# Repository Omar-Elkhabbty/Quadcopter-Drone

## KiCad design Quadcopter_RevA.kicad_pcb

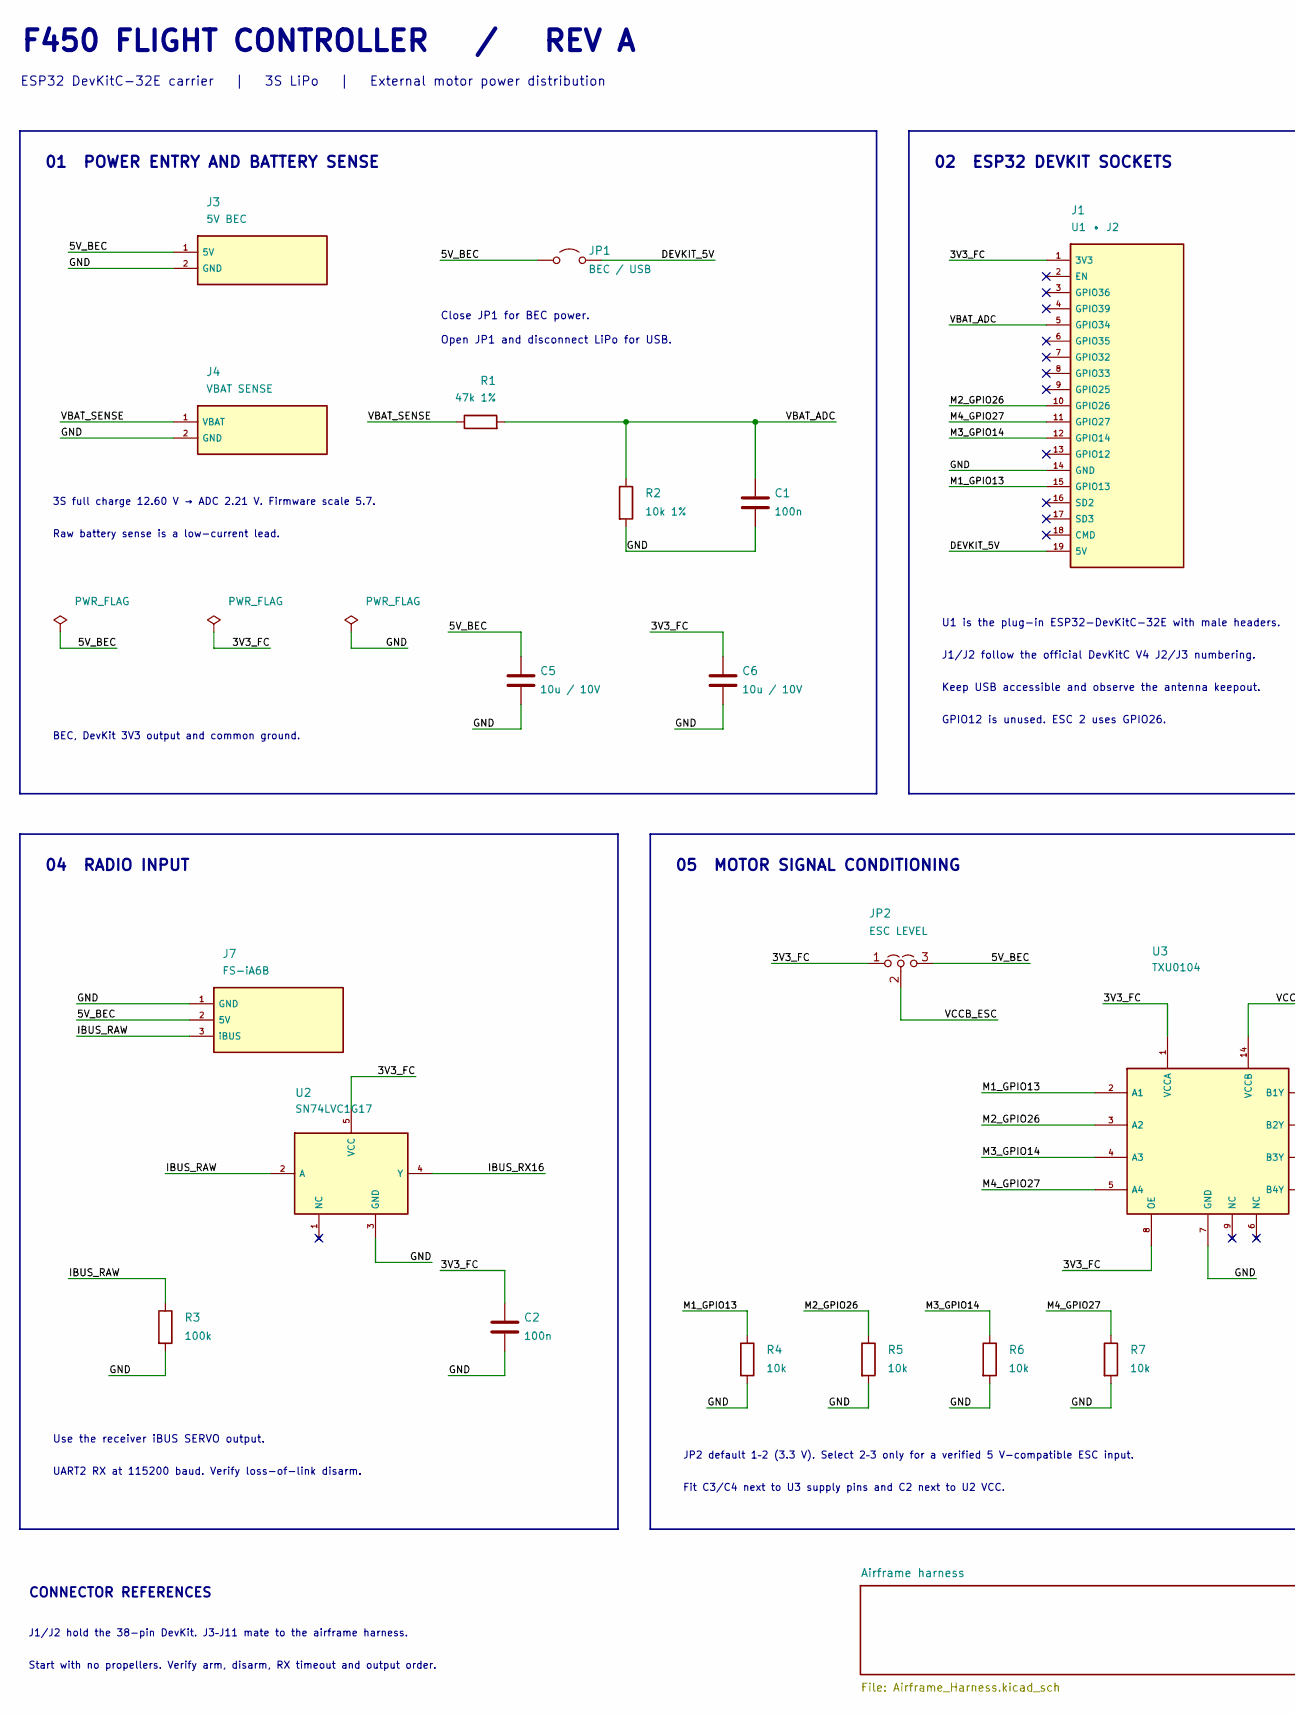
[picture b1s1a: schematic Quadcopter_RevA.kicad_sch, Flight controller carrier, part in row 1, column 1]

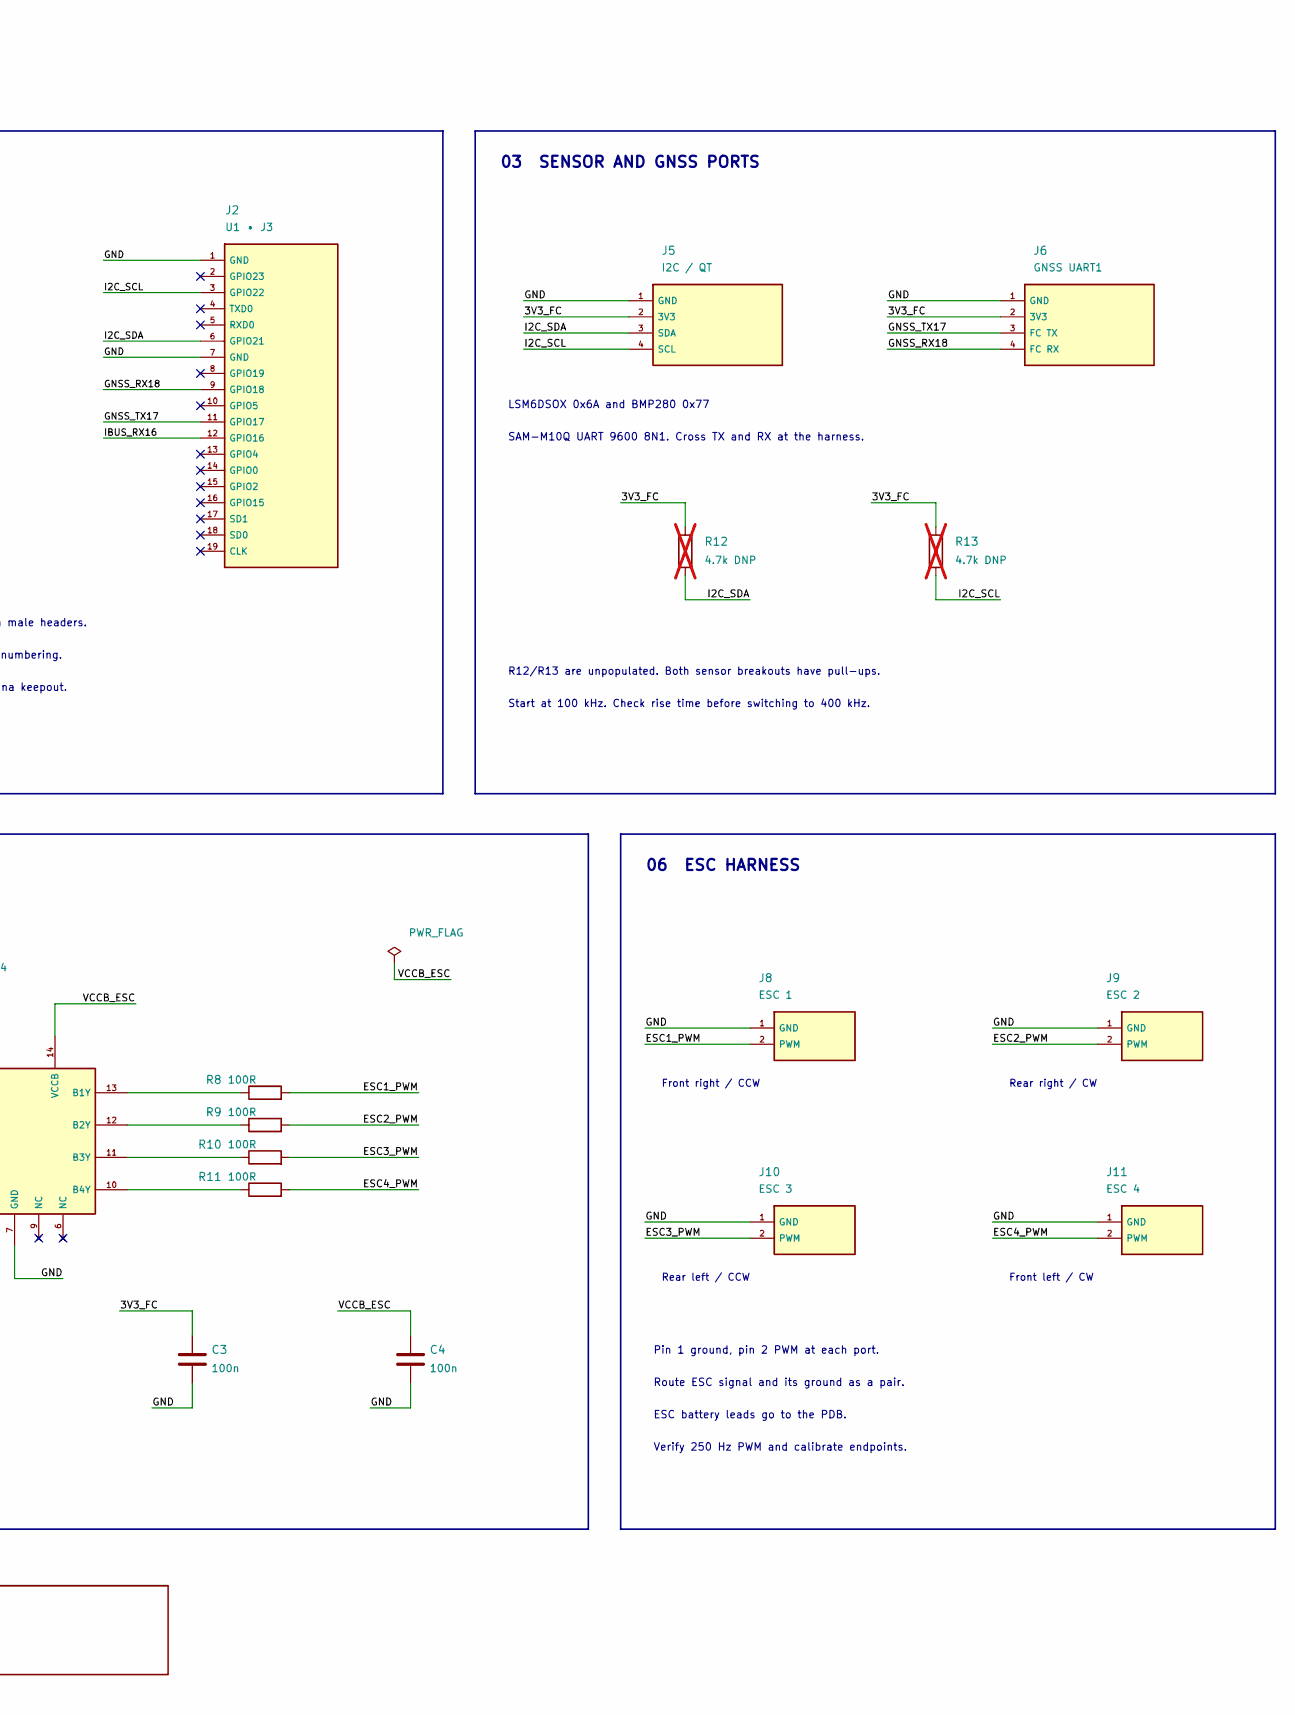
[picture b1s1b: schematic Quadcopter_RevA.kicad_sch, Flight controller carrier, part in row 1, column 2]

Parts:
C1, C2, C3, C4: 100n; C_0603_1608Metric; MPN GRM188R71H104KA93D
C5, C6: 10u / 10V; C_0805_2012Metric; MPN GRM21BR71A106KA73L
J1: U1 • J2; PinSocket_1x19_P2.54mm_Vertical; MPN SSW-119-01-G-S
J2: U1 • J3; PinSocket_1x19_P2.54mm_Vertical; MPN SSW-119-01-G-S
J3: 5V BEC; JST_VH_B2P-VH_1x02_P3.96mm_Vertical; MPN B2P-VH(LF)(SN)
J4: VBAT SENSE; SolderWire-0.127sqmm_1x02_P3.7mm_D0.48mm_OD1mm_Relief
J5: I2C / QT; JST_SH_SM04B-SRSS-TB_1x04-1MP_P1.00mm_Horizontal; MPN SM04B-SRSS-TB(LF)(SN)
J6: GNSS UART1; JST_XH_B4B-XH-A_1x04_P2.50mm_Vertical; MPN B4B-XH-A(LF)(SN)
J7: FS-iA6B; JST_XH_B3B-XH-A_1x03_P2.50mm_Vertical; MPN B3B-XH-A(LF)(SN)
J8: ESC 1; JST_XH_B2B-XH-A_1x02_P2.50mm_Vertical; MPN B2B-XH-A(LF)(SN)
J9: ESC 2; JST_XH_B2B-XH-A_1x02_P2.50mm_Vertical; MPN B2B-XH-A(LF)(SN)
J10: ESC 3; JST_XH_B2B-XH-A_1x02_P2.50mm_Vertical; MPN B2B-XH-A(LF)(SN)
J11: ESC 4; JST_XH_B2B-XH-A_1x02_P2.50mm_Vertical; MPN B2B-XH-A(LF)(SN)
JP1: BEC / USB; PinHeader_1x02_P2.54mm_Vertical; MPN TSW-102-07-G-S
JP2: ESC LEVEL; PinHeader_1x03_P2.54mm_Vertical; MPN TSW-103-07-G-S
R1: 47k 1%; R_0603_1608Metric; MPN RC0603FR-0747KL
R2: 10k 1%; R_0603_1608Metric; MPN RC0603FR-0710KL
R3: 100k; R_0603_1608Metric; MPN RC0603FR-07100KL
R4, R5, R6, R7: 10k; R_0603_1608Metric; MPN RC0603FR-0710KL
R8, R9, R10, R11: 100R; R_0603_1608Metric; MPN RC0603FR-07100RL
R12, R13: 4.7k DNP; R_0603_1608Metric; MPN RC0603FR-074K7L; not fitted
U2: SN74LVC1G17; SOT-23-5; MPN SN74LVC1G17DBVR
U3: TXU0104; TSSOP-14_4.4x5mm_P0.65mm; MPN TXU0104PWR

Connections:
/3V3_FC: C2.1, C3.1, C6.1, J1.1 (3V3), J5.2 (3V3), J6.2 (3V3), JP2.1 (A), R12.1, R13.1, U2.5 (VCC), U3.1 (VCCA), U3.8 (OE)
/5V_BEC: C5.1, J3.1 (5V), J7.2 (5V), JP1.1 (A), JP2.3 (B)
/DEVKIT_5V: J1.19 (5V), JP1.2 (B)
/ESC1_PWM: J8.2 (PWM), R8.2
/ESC2_PWM: J9.2 (PWM), R9.2
/ESC3_PWM: J10.2 (PWM), R10.2
/ESC4_PWM: J11.2 (PWM), R11.2
/GND: C1.2, C2.2, C3.2, C4.2, C5.2, C6.2, J1.14 (GND), J2.1 (GND), J2.7 (GND), J3.2 (GND), J4.2 (GND), J5.1 (GND), J6.1 (GND), J7.1 (GND), J8.1 (GND), J9.1 (GND), J10.1 (GND), J11.1 (GND), R2.2, R3.2, R4.2, R5.2, R6.2, R7.2, U2.3 (GND), U3.7 (GND)
/GNSS_RX18: J2.9 (GPIO18), J6.4 (FC RX)
/GNSS_TX17: J2.11 (GPIO17), J6.3 (FC TX)
/I2C_SCL: J2.3 (GPIO22), J5.4 (SCL), R13.2
/I2C_SDA: J2.6 (GPIO21), J5.3 (SDA), R12.2
/IBUS_RAW: J7.3 (iBUS), R3.1, U2.2 (A)
/IBUS_RX16: J2.12 (GPIO16), U2.4 (Y)
/M1_GPIO13: J1.15 (GPIO13), R4.1, U3.2 (A1)
/M2_GPIO26: J1.10 (GPIO26), R5.1, U3.3 (A2)
/M3_GPIO14: J1.12 (GPIO14), R6.1, U3.4 (A3)
/M4_GPIO27: J1.11 (GPIO27), R7.1, U3.5 (A4)
/VBAT_ADC: C1.1, J1.5 (GPIO34), R1.2, R2.1
/VBAT_SENSE: J4.1 (VBAT), R1.1
/VCCB_ESC: C4.1, JP2.2 (C), U3.14 (VCCB)
unnamed: R8.1, U3.13 (B1Y)
unnamed: R9.1, U3.12 (B2Y)
unnamed: R10.1, U3.11 (B3Y)
unnamed: R11.1, U3.10 (B4Y)

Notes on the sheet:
F450 FLIGHT CONTROLLER / REV A
ESP32 DevKitC-32E carrier | 3S LiPo | External motor power distribution
01 POWER ENTRY AND BATTERY SENSE
02 ESP32 DEVKIT SOCKETS
03 SENSOR AND GNSS PORTS
04 RADIO INPUT
05 MOTOR SIGNAL CONDITIONING
06 ESC HARNESS
Close JP1 for BEC power.
Open JP1 and disconnect LiPo for USB.
3S full charge 12.60 V → ADC 2.21 V. Firmware scale 5.7.
Raw battery sense is a low-current lead.
BEC, DevKit 3V3 output and common ground.
U1 is the plug-in ESP32-DevKitC-32E with male headers.
J1/J2 follow the official DevKitC V4 J2/J3 numbering.
Keep USB accessible and observe the antenna keepout.
GPIO12 is unused. ESC 2 uses GPIO26.
LSM6DSOX 0x6A and BMP280 0x77
SAM-M10Q UART 9600 8N1. Cross TX and RX at the harness.
R12/R13 are unpopulated. Both sensor breakouts have pull-ups.
Start at 100 kHz. Check rise time before switching to 400 kHz.
Use the receiver iBUS SERVO output.
UART2 RX at 115200 baud. Verify loss-of-link disarm.
JP2 default 1–2 (3.3 V). Select 2–3 only for a verified 5 V-compatible ESC input.
Fit C3/C4 next to U3 supply pins and C2 next to U2 VCC.
Front right / CCW
Rear right / CW
Rear left / CCW
Front left / CW
Pin 1 ground, pin 2 PWM at each port.
Route ESC signal and its ground as a pair.
ESC battery leads go to the PDB.
Verify 250 Hz PWM and calibrate endpoints.
CONNECTOR REFERENCES
J1/J2 hold the 38-pin DevKit. J3–J11 mate to the airframe harness.
Start with no propellers. Verify arm, disarm, RX timeout and output order.

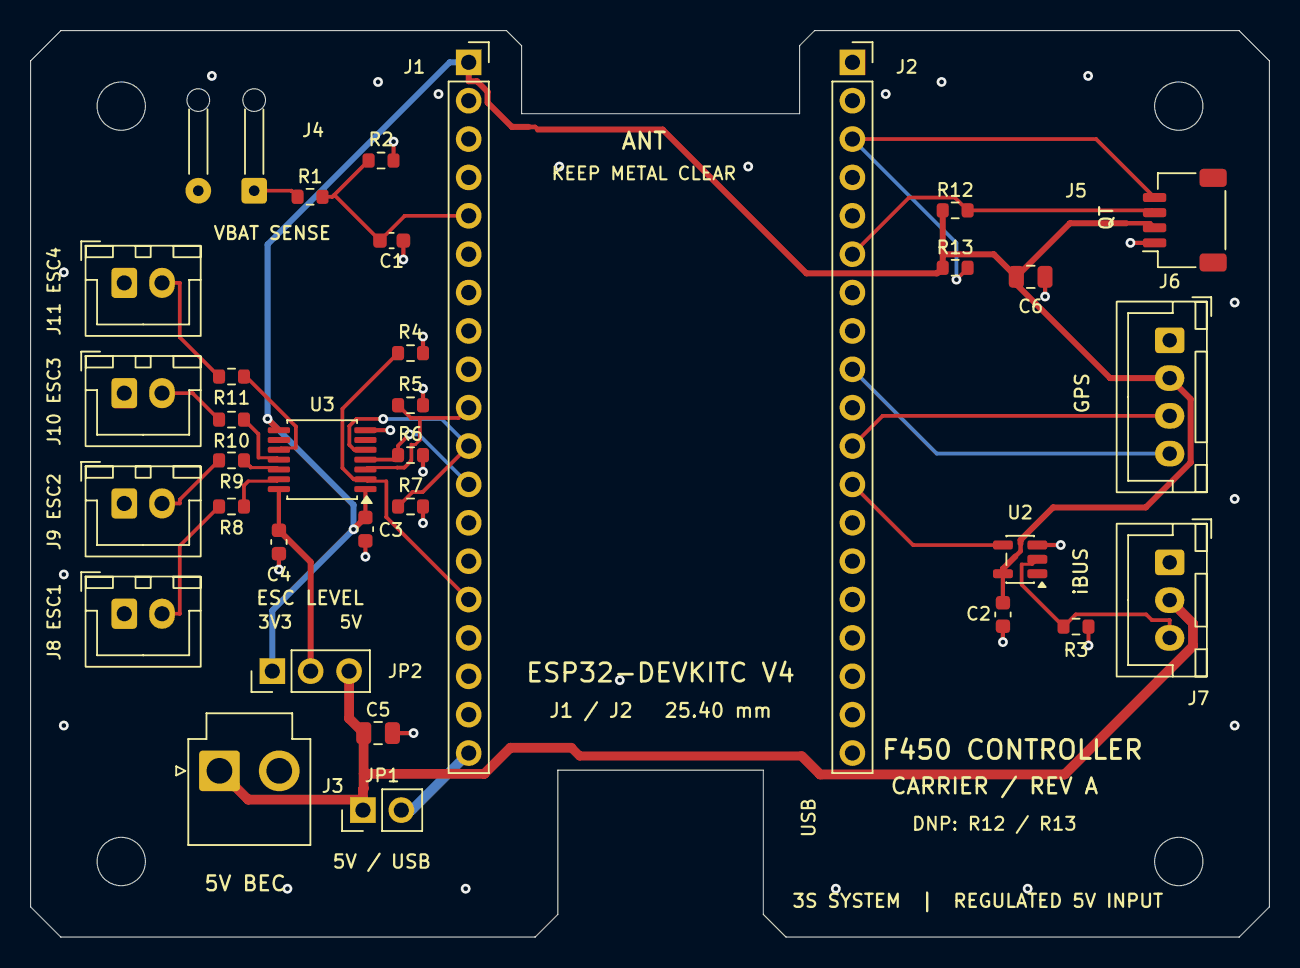
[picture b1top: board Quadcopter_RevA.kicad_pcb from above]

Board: 4 copper layers, 82.0 x 60.0 mm, 38 parts (0 on the bottom side), 25 nets.

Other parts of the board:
H1, H2, H3, H4: M3 NPTH; MountingHole_3.2mm_M3
